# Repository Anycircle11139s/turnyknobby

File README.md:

# turnyknobby
I made a turny knobby thingy cause I wanted my desk to look cooooolll. So i can be reall tuff and flex my sigma-ness to all my friends, I also throught it would be really fun to design and build, and so far, I'm right. I wanted to be able to control my volume without spamming my volume increase buttons, and I wanted the thing to be bluetooth, cause I don't like wires clutering up my desk.

I started with the custom PCB, I kind of based the PCB off a blinky board, except it has a microcontroller and no random other stuff, just microcontroller connected to leds with a rotary encoder for the turning. I chose the xiao esp32-s3 ecause of its bluetooth capabilities and after finishing my schematic, I started on the PCB. I made circle as the edges of the PCB and put the LEDs in a circle around the edges so they can display how high my volume is. I made sure the rotary encoder was in the exact middle, so when I turn it (there will be a case on top) the case wont look weird. After tracing it up, I finished the PCB.
<br>

<br>
Once I finsihed the PCB, I moved on to the CAD. Before I could fully begin with CADing the case, I had to get all my 3d models imported, and to do that, I would have to decide which lipo battery I would use. I spent a while trying to decide and I made sure the one I chose had a 3d model of it, so I could cad it into the case. Once I had all my 3d models imported, I moved on to actually creating the case. I started by creating the bottom and frame, like I always do, created the turn thingy and made a hole for the rotary encoder, so that when I turn the case, it turns the rotary encoder. Then, I created some slots for the lid in the bottom part of the case, so it fits properly. After that, I added supports for the PCB and lipo battery, and with that, I finsihed the CAD.
<br>
<br>

<br>

After that, I made some simple code and I had finally finished my design, I hope this gets approved soon, so I can order my parts and build this thing.

<br>
BOM
<br>
<br>

|Name               |Purpose                                           |Quantity|Total Cost (USD)|Link                                                                                                                                                                                                                                                                                                                                                                                                                                                                                                                                                                                                                                                                                                                                                                              |Distributor    |
|-------------------|--------------------------------------------------|--------|----------------|----------------------------------------------------------------------------------------------------------------------------------------------------------------------------------------------------------------------------------------------------------------------------------------------------------------------------------------------------------------------------------------------------------------------------------------------------------------------------------------------------------------------------------------------------------------------------------------------------------------------------------------------------------------------------------------------------------------------------------------------------------------------------------|---------------|
|leds 200 pack      |fo lights                                         |1       |0.99            |https://www.aliexpress.com/item/1005005634821961.html?spm=a2g0o.productlist.main.1.62e031f8KIq3fX&algo_pvid=e44b5a7c-2a0b-4f1c-88f1-c361ff9a790c&algo_exp_id=e44b5a7c-2a0b-4f1c-88f1-c361ff9a790c-0&pdp_ext_f=%7B%22order%22%3A%221509%22%2C%22spu_best_type%22%3A%22price%22%2C%22eval%22%3A%221%22%2C%22fromPage%22%3A%22search%22%7D&pdp_npi=6%40dis%21USD%219.63%210.99%21%21%2165.31%216.69%21%402101e80f17767298899571692e018c%2112000033829717788%21sea%21AU%217402515296%21X%211%210%21n_tag%3A-29911%3Bd%3Aef1e07f3%3Bm03_new_user%3A-29895%3BpisId%3A5000000204047332&curPageLogUid=Mgm9GSmPmAsB&utparam-url=scene%3Asearch%7Cquery_from%3A%7Cx_object_id%3A1005005634821961%7C_p_origin_prod%3A                                                                        |Ali express    |
|100 ohm resistor   |so led dont explode                               |20      |0.99            |https://www.aliexpress.com/item/1005011767578775.html?spm=a2g0o.productlist.main.4.730f2180T2PxcI&aem_p4p_detail=20260420170207960599008190850002510507&algo_pvid=adaaadbb-82d0-41ef-99db-d2e7fab36f45&algo_exp_id=adaaadbb-82d0-41ef-99db-d2e7fab36f45-3&pdp_ext_f=%7B%22order%22%3A%22291%22%2C%22eval%22%3A%221%22%2C%22fromPage%22%3A%22search%22%7D&pdp_npi=6%40dis%21USD%212.27%210.99%21%21%2115.42%216.74%21%40210311a017767297269087603e99cd%2112000056498243050%21sea%21AU%217402515296%21X%211%210%21n_tag%3A-29911%3Bd%3Aef1e07f3%3Bm03_new_user%3A-29895%3BpisId%3A5000000204047332&curPageLogUid=Gnwk2xyWiiBt&utparam-url=scene%3Asearch%7Cquery_from%3A%7Cx_object_id%3A1005011767578775%7C_p_origin_prod%3A&search_p4p_id=20260420170207960599008190850002510507_1|ali express    |
|ec11 rotary encoder|to rotary encode and act as a knob                |1       |0.99            |https://www.aliexpress.com/item/1005007644083514.html?spm=a2g0o.productlist.main.1.3624286f1sM9NP&algo_pvid=cc7b006b-38e9-452d-9a69-8516b33908d8&algo_exp_id=cc7b006b-38e9-452d-9a69-8516b33908d8-0&pdp_ext_f=%7B%22order%22%3A%222768%22%2C%22spu_best_type%22%3A%22price%22%2C%22eval%22%3A%221%22%2C%22fromPage%22%3A%22search%22%7D&pdp_npi=6%40dis%21USD%211.17%210.99%21%21%211.17%210.99%21%40210311a017767295759822388e99ce%2112000041630839415%21sea%21AU%217402515296%21X%211%210%21n_tag%3A-29911%3Bd%3Aef1e07f3%3Bm03_new_user%3A-29895%3BpisId%3A5000000204047332&curPageLogUid=Nx3W1n9aBMlm&utparam-url=scene%3Asearch%7Cquery_from%3A%7Cx_object_id%3A1005007644083514%7C_p_origin_prod%3A                                                                         |ali express    |
|Xiao esp32 s3      |microcontroller                                   |1       |14.11           |https://www.aliexpress.com/item/1005007437214568.html?spm=a2g0o.productlist.main.9.1b823fc9UTre3r&algo_pvid=b1f963bd-0d49-4943-8d2f-2f43d8367fe8&algo_exp_id=b1f963bd-0d49-4943-8d2f-2f43d8367fe8-8&pdp_ext_f=%7B%22order%22%3A%2239%22%2C%22eval%22%3A%221%22%2C%22fromPage%22%3A%22search%22%7D&pdp_npi=6%40dis%21USD%2114.11%2114.11%21%21%2195.70%2195.70%21%402101e80f17767293201301004e0187%2112000040753490813%21sea%21AU%210%21ABX%211%210%21n_tag%3A-29910%3Bd%3Aef1e07f3%3Bm03_new_user%3A-29895&curPageLogUid=NxnPvcEwhNcO&utparam-url=scene%3Asearch%7Cquery_from%3A%7Cx_object_id%3A1005007437214568%7C_p_origin_prod%3A                                                                                                                                             |Ali express    |
|lipo battery       |the battery of the thing so I can make it wireless|1       |1.50            |https://www.aliexpress.com/item/1005009240348340.html?spm=a2g0o.productlist.main.5.714b193bY0YTTY&algo_pvid=a573cc3b-1634-4cda-8c05-e6a4fd07404b&algo_exp_id=a573cc3b-1634-4cda-8c05-e6a4fd07404b-4&pdp_ext_f=%7B%22order%22%3A%22716%22%2C%22eval%22%3A%221%22%2C%22fromPage%22%3A%22search%22%7D&pdp_npi=6%40dis%21USD%2115.55%211.43%21%21%2115.55%211.43%21%402101c59117767303230154473ee6df%2112000048437368273%21sea%21AU%217402515296%21X%211%210%21n_tag%3A-29911%3Bd%3Aef1e07f3%3Bm03_new_user%3A-29895%3BpisId%3A5000000204047332&curPageLogUid=MOPpWXzbwn9I&utparam-url=scene%3Asearch%7Cquery_from%3A%7Cx_object_id%3A1005009240348340%7C_p_origin_prod%3A                                                                                                            |ali express    |
|Case               |to hold everything together                       |1       |6.50            |                                                                                                                                                                                                                                                                                                                                                                                                                                                                                                                                                                                                                                                                                                                                                                                  |Printing legion|
|PCB                |To hold the components together                   |1       |5.50            |                                                                                                                                                                                                                                                                                                                                                                                                                                                                                                                                                                                                                                                                                                                                                                                  |JLCPCB         |

## Building it IRL
I soldered the components together and spent like 3 hours debugging the code, in doing so, I realised because all the pins were taken and requiring a lot of energy (I only put 100r resistors on the LEDs), the thing would crash whenever trying to connect to bluetooth. Because of this, I had to remove the bluetooth volume control feature but atleast the lights work.

https://github.com/user-attachments/assets/500954ba-3ecc-4af9-afe1-6bbe065ede46

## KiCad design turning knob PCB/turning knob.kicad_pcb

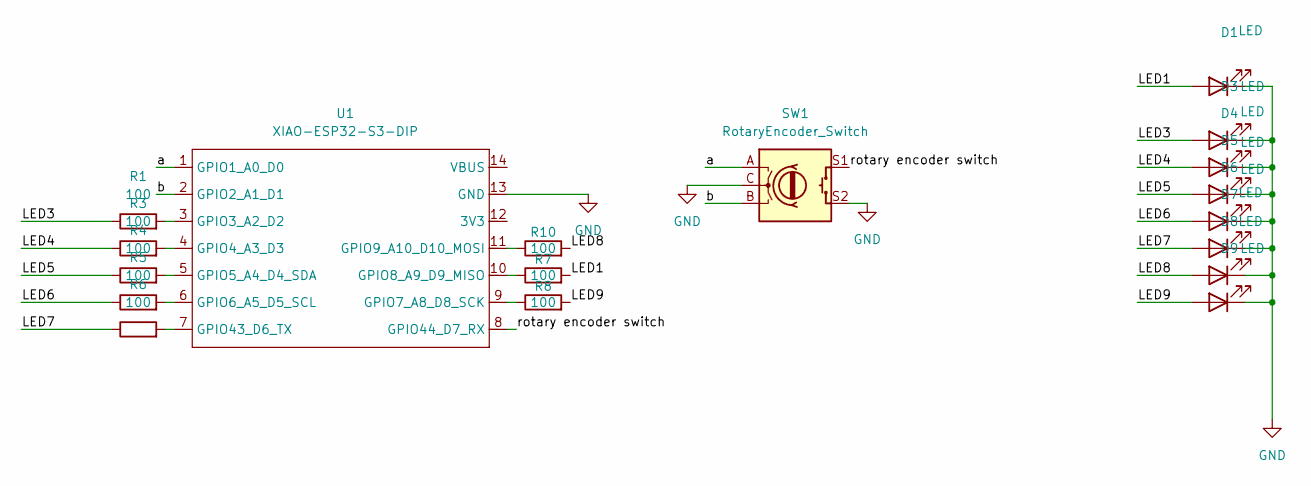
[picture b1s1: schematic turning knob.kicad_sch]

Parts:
D1, D3, D4, D5, D6, D7, D8, D9: LED; LED_D3.0mm
R1, R3, R4, R5, R6, R7, R8, R10: 100; R_Axial_DIN0207_L6.3mm_D2.5mm_P7.62mm_Horizontal
SW1: RotaryEncoder_Switch; RotaryEncoder_Alps_EC11E-Switch_Vertical_H20mm
U1: XIAO-ESP32-S3-DIP

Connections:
/LED1: D1.2 (A), R7.2
/LED3: D3.2 (A), R1.1
/LED4: D4.2 (A), R3.1
/LED5: D5.2 (A), R4.1
/LED6: D6.2 (A), R5.1
/LED7: D7.2 (A), R6.1
/LED8: D8.2 (A), R10.2
/LED9: D9.2 (A), R8.2
/a: SW1.A, U1.1 (GPIO1_A0_D0)
/b: SW1.B, U1.2 (GPIO2_A1_D1)
/rotary encoder switch: SW1.S1, U1.8 (GPIO44_D7_RX)
GND: D1.1 (K), D3.1 (K), D4.1 (K), D5.1 (K), D6.1 (K), D7.1 (K), D8.1 (K), D9.1 (K), SW1.C, SW1.S2, U1.13 (GND)
unnamed: R1.2, U1.3 (GPIO3_A2_D2)
unnamed: R3.2, U1.4 (GPIO4_A3_D3)
unnamed: R4.2, U1.5 (GPIO5_A4_D4_SDA)
unnamed: R5.2, U1.6 (GPIO6_A5_D5_SCL)
unnamed: R8.1, U1.9 (GPIO7_A8_D8_SCK)
unnamed: R7.1, U1.10 (GPIO8_A9_D9_MISO)
unnamed: R10.1, U1.11 (GPIO9_A10_D10_MOSI)
unnamed: R6.2, U1.7 (GPIO43_D6_TX)

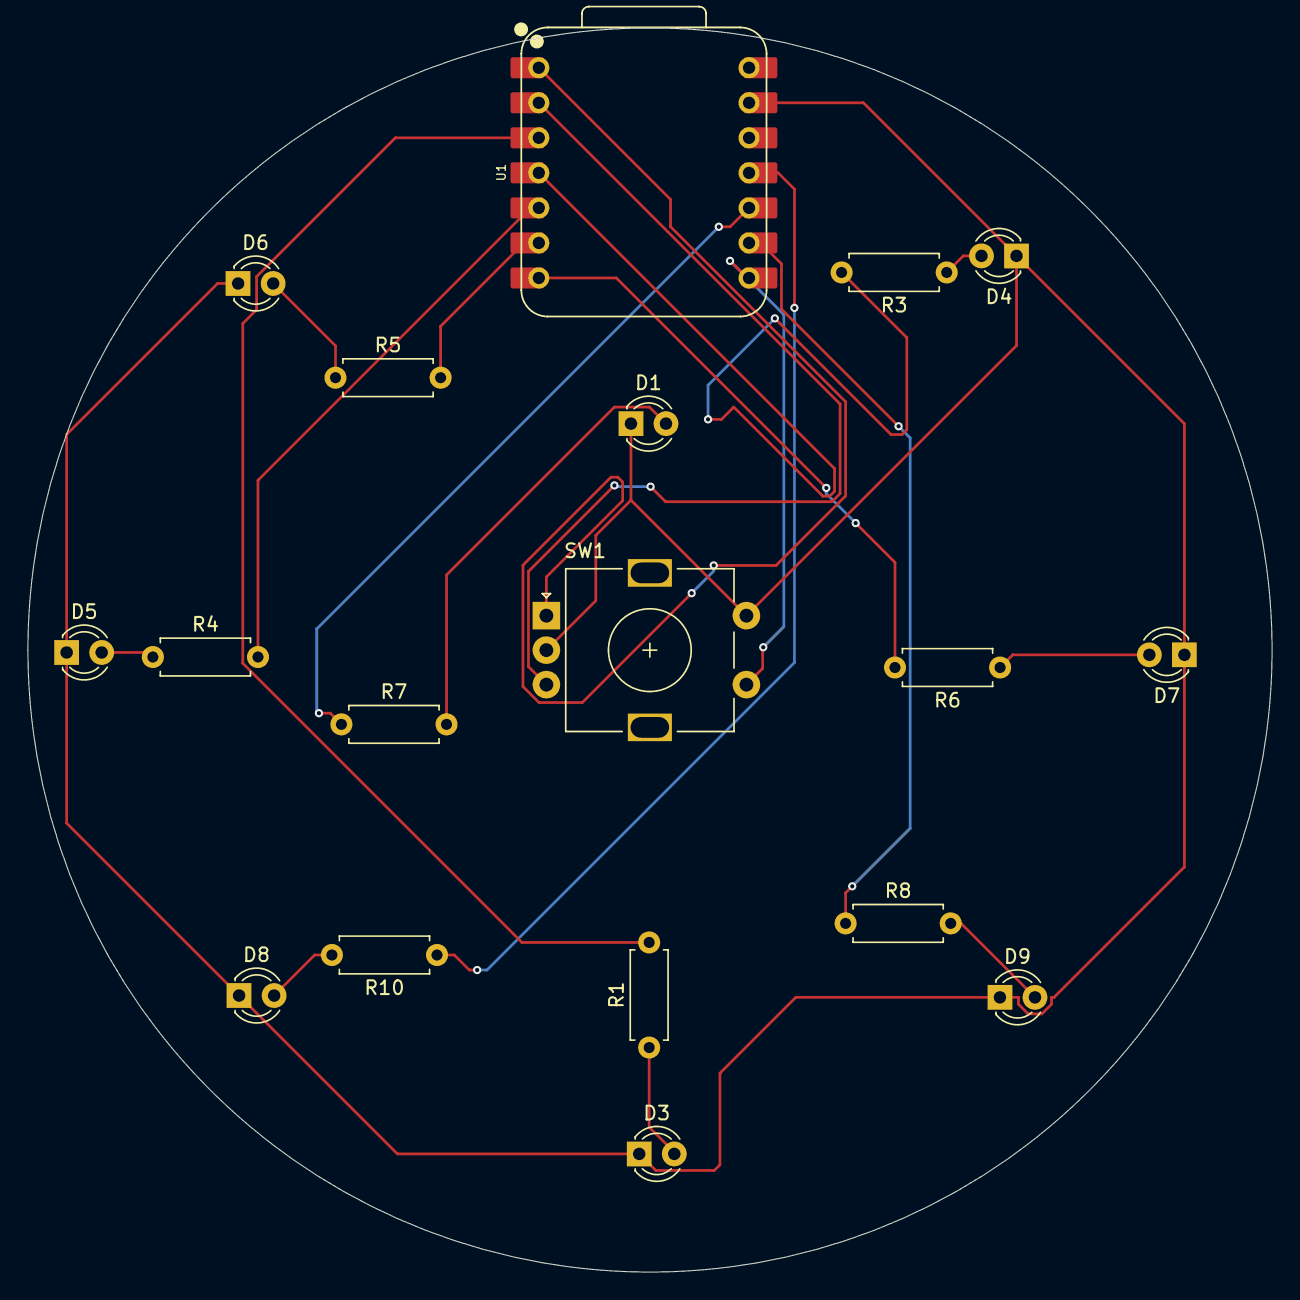
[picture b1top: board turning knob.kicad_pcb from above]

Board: 2 copper layers, 90.2 x 90.2 mm, 18 parts (0 on the bottom side), 20 nets.
